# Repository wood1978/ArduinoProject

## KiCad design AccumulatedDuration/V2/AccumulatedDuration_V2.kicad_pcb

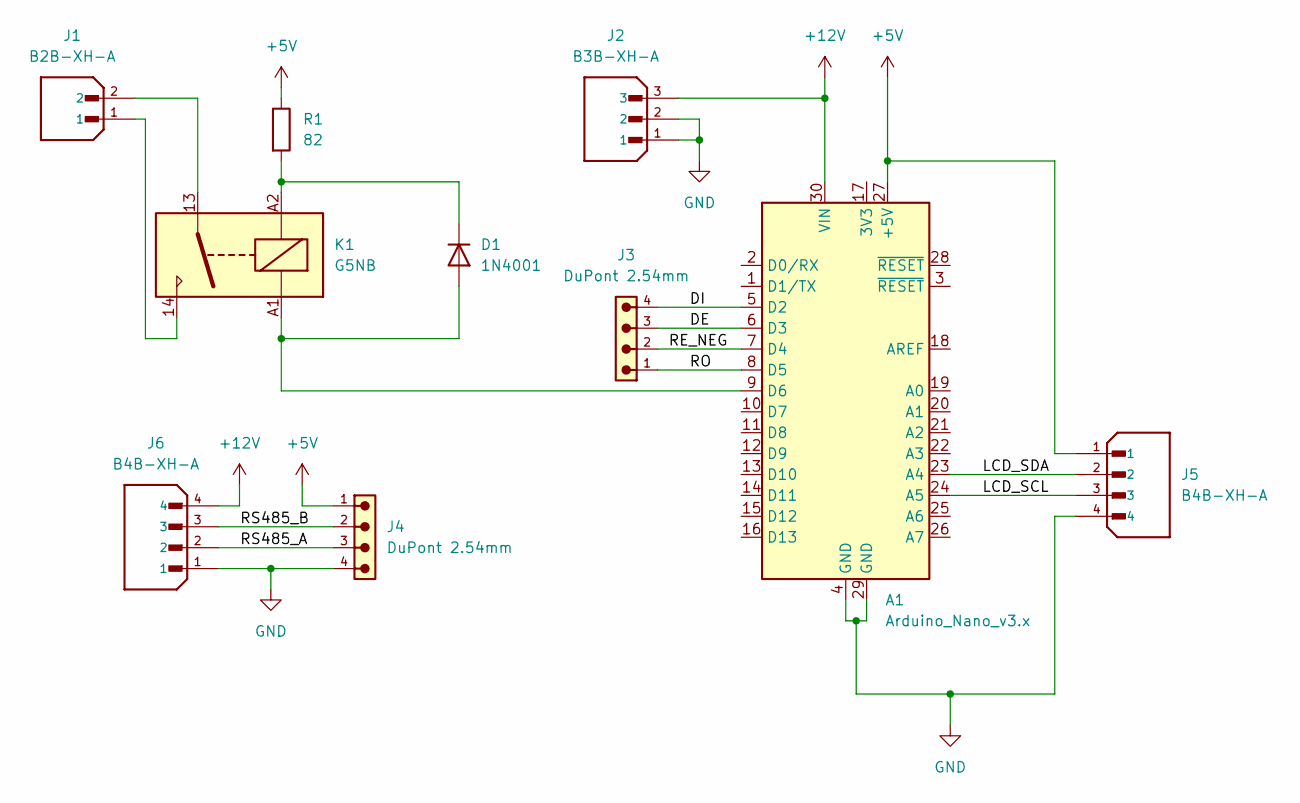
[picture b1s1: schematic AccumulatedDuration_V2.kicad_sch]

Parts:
A1: Arduino_Nano_v3.x; Arduino_Nano
D1: 1N4001; D_DO-41_SOD81_P10.16mm_Horizontal
J1: B2B-XH-A; JST_B2B-XH-A; PARTREV N/A
J2: B3B-XH-A; JST_B3B-XH-A; PARTREV 7/4/21
J3, J4: DuPont 2.54mm; 61300411121
J5, J6: B4B-XH-A; JST_B4B-XH-A; PARTREV 7/4/21
K1: G5NB; Relay_SPST_Omron_G5NB
R1: 82; R_Axial_DIN0309_L9.0mm_D3.2mm_P12.70mm_Horizontal

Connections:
+5V: A1.27 (+5V), J4.1, J5.1, R1.1
+12V: A1.30 (VIN), J2.3, J6.4
/DE: A1.6 (D3), J3.3
/DI: A1.5 (D2), J3.4
/LCD_SCL: A1.24 (A5), J5.3
/LCD_SDA: A1.23 (A4), J5.2
/RE_NEG: A1.7 (D4), J3.2
/RO: A1.8 (D5), J3.1
/RS485_A: J4.3, J6.2
/RS485_B: J4.2, J6.3
GND: A1.4 (GND), A1.29 (GND), J2.1, J2.2, J4.4, J5.4, J6.1
unnamed: A1.9 (D6), D1.2 (A), K1.A1
unnamed: D1.1 (K), K1.A2, R1.2
unnamed: J1.1, K1.14
unnamed: J1.2, K1.13

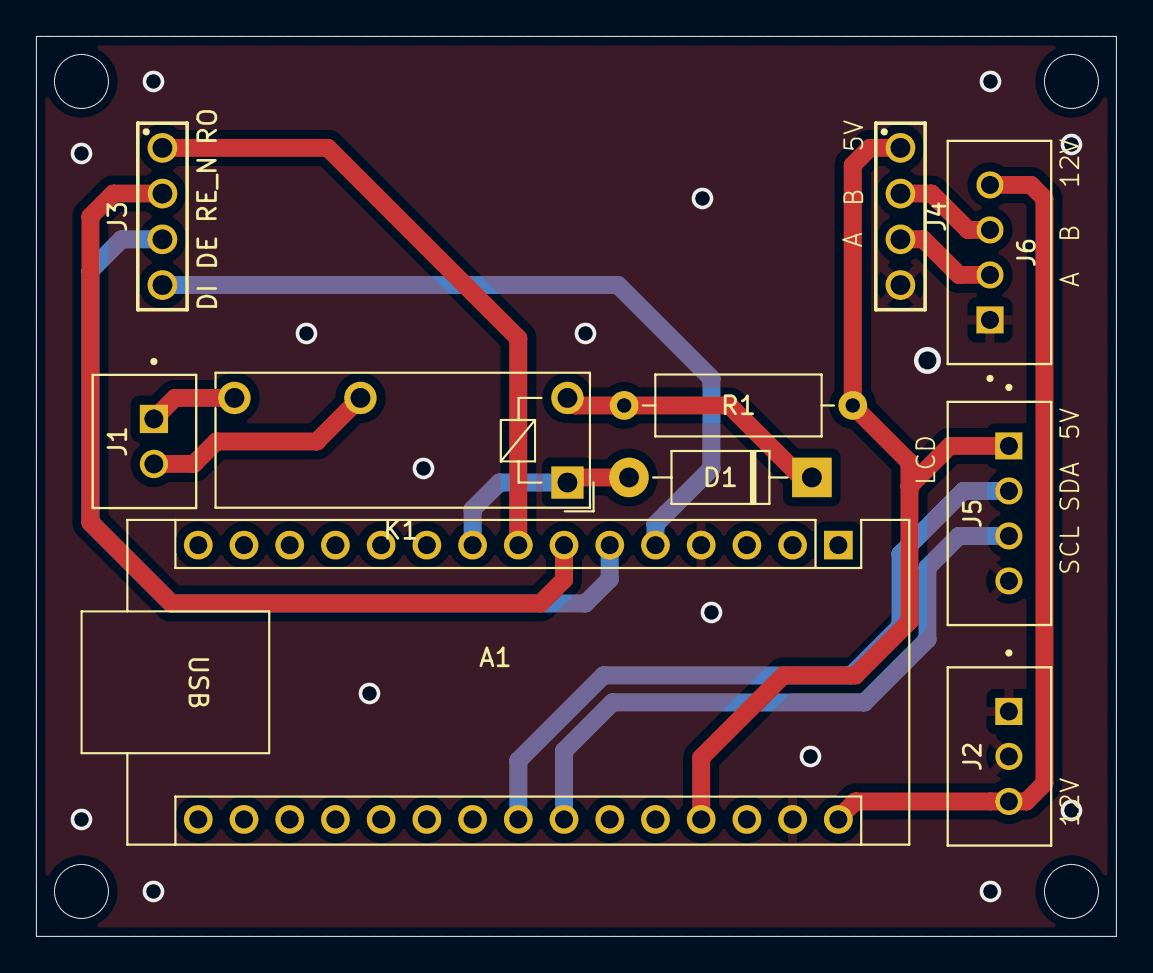
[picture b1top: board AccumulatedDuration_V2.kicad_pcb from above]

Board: 2 copper layers, 60.0 x 50.0 mm, 10 parts (0 on the bottom side), 15 nets.

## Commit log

2025-05-14 * Add common for hardware.
2025-05-15 * Move DJ Disk to DjDisk directory.
2025-05-18 * Add AccumulatedDuration source code.
2025-05-19 * Change accumlated time display format. * Remove reset time function.
2025-05-25 * Extend EEPROM life time.
2025-07-07 * Add V2 hardware file.
2025-07-08 * Add AccumulatedDuration V1 hardware file.
2025-07-11 * Firmware changes for AccumulatedDuration v2 hardware.
2025-07-11 * Release AccumulatedDuration v2 hardware.
2025-07-19 * Add models for design PCB
2025-07-20 * Modify AccumulatedDuration V2 layout.
2025-07-29 * AccumulatedDuration_V2 sch add no connect.
2025-08-02 * AccumulatedDuration_V2 use alarm1 enable relay and alarm2 disable relay.
